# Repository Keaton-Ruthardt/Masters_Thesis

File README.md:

# An Instrumented Baseball for Per-Finger Grip Force Measurement

Reproducibility materials for the MS thesis *An Instrumented Baseball for Per-Finger
Grip Force Measurement: Finger Force Tracks Delivery Effort Rather Than Release Velocity*
(Keaton Ruthardt, MS Computer Science — Data Science, Oral Roberts University, 2026).

A regulation baseball instrumented with four thin-film force sensors under the leather
cover, sampling all channels at 480 Hz and streaming over Bluetooth Low Energy, paired
per pitch with TrackMan radar release velocity.

## What the study found

Measured the way the field currently measures it — with a graded submaximal effort
ladder — grip force predicts release velocity strongly and broadly: index + middle
force at release reaches *r* = 0.59, and 15 of 20 grip features remain significant
after Holm correction.

Holding commanded effort fixed removes that association. Index + middle force at
release falls to *r* = 0.33 (n.s.), and its unique contribution to velocity variance
is **ΔR² = 0.000**, against 0.743 for commanded effort alone. A mixed-effects model
agrees (χ²(1) = 0.47, *p* = 0.49).

Three thumb-dominated features survive Benjamini–Hochberg correction (*q* = 0.035);
none clears family-wise correction, and all are reported as **exploratory**.

The conclusion is that finger grip force, measured under a submaximal effort protocol,
is largely a readout of delivery effort rather than a determinant of release velocity.

## Layout

| Path | Contents |
|---|---|
| `thesis/` | The thesis (`MSCS_Paper.docx`) and its Quarto source, bibliography, and CSL style |
| `defense/` | Defense presentation, including a copy with speaker notes |
| `Masters_Thesis_and_Defense.zip` | Thesis and presentation bundled together |
| `firmware/` | Arduino sketches for the Seeed XIAO nRF52840 |
| `acquisition/` | `ble_logger.py` — BLE client, writes raw counts to CSV |
| `calibration/` | Per-sensor calibration procedure, fitting script, factors, raw captures |
| `analysis/` | Feature extraction, statistics, and figure generation |
| `analysis/results/` | Derived, de-identified data and generated statistical reports |
| `figures/` | Figures as they appear in the thesis |
| `hardware/` | KiCad PCB project, schematic and layout PDFs, bill of materials |
| `docs/` | Illustrated build guides, project plan, proposal |

### Firmware

- `pressure_logger_480/` — **deployed** acquisition firmware. 480 Hz, four samples per packet.
- `pressure_logger/` — earlier 120 Hz single-sample version; the host logger supports both.
- `isolation_test/` — channel-isolation gate.
- `sensor_test/`, `single_sensor/`, `calibrate_sensors/` — bench-check sketches.

Built with the Arduino IDE and the Seeed nRF52 **mbed-enabled** board package. The
non-mbed package fails to link.

## Wire protocol

The pressure characteristic carries a **36-byte packet**: a 32-bit unsigned microsecond
timestamp for the first sample in the batch, followed by four sample groups of four
16-bit unsigned ADC values each, little-endian, in channel order S1 through S4. Sample
*k* within a batch occurs at the batch timestamp plus *k* × 2083 µs.

The earlier firmware sends a 12-byte packet: a 32-bit millisecond timestamp followed by
four 16-bit ADC values. `ble_logger.py` derives the batch size from the packet length
and works against either version without modification.

## Data dictionary

Each logged CSV row contains:

| Column | Meaning |
|---|---|
| `wall_iso` | Host wall-clock time, ISO 8601, UTC |
| `wall_unix_ms` | Host wall-clock time, integer ms since the Unix epoch |
| `ball_t_ms` | The instrument's own timebase in ms — **the authoritative timing column** |
| `s1`–`s4` | Raw ADC counts, 0–4095, in channel order |
| `s1_N`–`s4_N` | Convenience force values in newtons |
| `marker` | Operator-typed per-pitch tag (pitch id, effort, outcome) |

Raw counts are the archived source of truth. Calibration is applied downstream in
analysis, never on the ball, so it can be revised without re-collecting data.

## Force conversion

For a sensor of resistance *R*ₛ in series with a fixed 10 kΩ resistor, the divider node
read by the 12-bit ADC gives a conductance ratio

```
G = ADC / (4095 - ADC)
F = c * G
```

where *c* is the per-sensor calibration factor in `calibration/calfactors_v3.csv`,
fitted through the origin by least squares over twenty applied-mass trials per sensor
(R² = 0.961 to 0.995).

## Reproducing the analysis

```bash
pip install numpy pandas scipy statsmodels matplotlib
cd analysis
python thesis_analysis_v2.py     # feature extraction -> results/
python advanced_stats.py         # corrections, variance decomposition, bootstrap
python make_thesis_figures.py    # figures
```

A fixed random seed (20260805) makes every reported *p*-value reproducible: 20,000
permutations and 10,000 bootstrap resamples throughout.

Note that `thesis_analysis_v2.py` reads raw session captures, which are not distributed
here (see below). The derived feature table it produces, `analysis/results/per_pitch_features.csv`,
**is** included, and `advanced_stats.py` and `make_thesis_figures.py` run from it directly.

## Participant data

Raw per-pitch session captures are **not included**, in accordance with the
participant-privacy commitments described in the thesis. Participants consented to their
data being used in the study; that consent did not extend to public redistribution of
raw records.

Derived, de-identified summary data sufficient to reproduce the reported figures and
models are provided in `analysis/results/`. Pitchers are identified only as P1, P2, P3.

## Licensing

- **Code and firmware** — [MIT License](LICENSE)
- **Documentation, figures, and build records** — [CC BY 4.0](LICENSE-DOCS)

Both are permissive and allow reuse with attribution, which is the intent for a
reproducibility release: you should be able to rebuild the instrument and re-run the
analysis without seeking further permission.

Third-party software is used in accordance with its own licenses, none of which impose
copyleft obligations on this project's code. TrackMan, PitchLogic, Kookaburra,
FlexiForce, Tekscan, Seeed, and Nordic Semiconductor are trademarks of their respective
owners, used nominatively to identify the products actually used or discussed. No
endorsement is implied.

## Safety

The instrument places a lithium-polymer cell and rigid electronics inside a ball thrown
at speed. If you rebuild it, read `docs/BALL_INTEGRATION_GUIDE.md` first. Epoxy is poured
in ~15 g layers with each cured before the next, because the exotherm of a single large
pour is a genuine thermal hazard to an enclosed LiPo cell, and the cell is wrapped before
potting. The ball is retired — not repaired — if the cover is breached, the potted block
loosens, the cell swells or fails to hold charge, or the channel-isolation test fails
after an impact. The cell cannot be removed once potted, so retirement means disposal of
the whole assembly through appropriate lithium-battery disposal.

## Citation

```bibtex
@mastersthesis{ruthardt2026instrumented,
  author = {Ruthardt, Keaton},
  title  = {An Instrumented Baseball for Per-Finger Grip Force Measurement:
            Finger Force Tracks Delivery Effort Rather Than Release Velocity},
  school = {Oral Roberts University},
  year   = {2026},
  type   = {MS thesis}
}
```

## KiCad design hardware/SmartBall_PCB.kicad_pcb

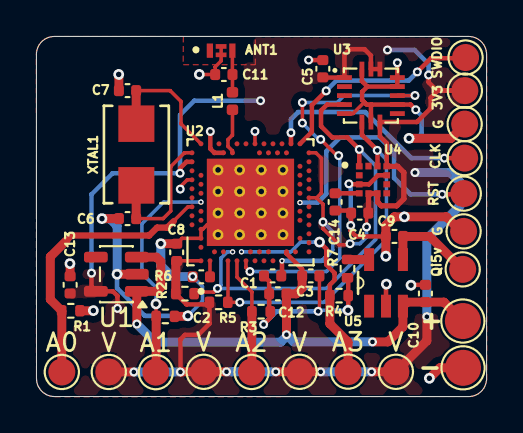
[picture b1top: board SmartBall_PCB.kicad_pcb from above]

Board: 2 copper layers, 25.0 x 20.0 mm, 46 parts (0 on the bottom side), 21 nets.

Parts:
3V3: PAD1; TestPoint_Pad_D1.5mm
+: PAD1; TestPoint_Pad_D2.0mm
-: PAD1; TestPoint_Pad_D2.0mm
A0, A1, A2, A3: PAD1; TestPoint_Pad_D1.5mm
ANT1: ANT016008LCS2442MA1; ANT_ANT016008LCS2442MA1
C1, C2, C4, C5, C14: 100nF/16V; C_0402_1005Metric
C3: 1uF/16V X7R; C_0402_1005Metric
C6, C7: 12pF/16V; C_0402_1005Metric
C8: 10uF/10V X5R; C_0402_1005Metric
C9, C10: 4.7uF/16V X5R; C_0402_1005Metric
C11: 1pF/50V; C_0402_1005Metric
C12, C13: 1uF/10V X7R; C_0402_1005Metric
CLK: PAD1; TestPoint_Pad_D1.5mm
G: PAD1; TestPoint_Pad_D1.5mm
G#2: PAD1; TestPoint_Pad_D1.5mm
L1: 2.2uH; L_0402_1005Metric
Qi5v: PAD1; TestPoint_Pad_D1.5mm
R1, R2, R3, R4: 10K; R_0402_1005Metric
R5, R6: 4.7K; R_0402_1005Metric
R7: 2K; R_0402_1005Metric
RST: PAD1; TestPoint_Pad_D1.5mm
SWDIO: PAD1; TestPoint_Pad_D1.5mm
U1: AP2112K-3.3; SOT-23-5
U2: NRF52840-QIAA-R; XCVR_NRF52840-QIAA-R
U3: H3LIS331DLTR; QFN300X300X100-16N
U4: LIS3MDLTR; XDCR_LIS3MDLTR
U5: MCP73831T-2ACI_OT; SOT95P280X145-5N
V: PAD1; TestPoint_Pad_D1.5mm
V#2, V#3, V#4: PAD1; TestPoint_Pad_D1.5mm
XTAL1: X50328MSB2GI; XTAL_MSB2GI_YXC

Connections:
/AIN0: A0.1 (1_1), R1.1, U2.A12 (P0.02/AIN0)
/AIN1: A1.1 (1_1), R2.1, U2.B13 (P0.03/AIN1)
/AIN2: A2.1 (1_1), R3.1, U2.J1 (P0.04/AIN2)
/AIN3: A3.1 (1_1), R4.1, U2.K2 (P0.05/AIN3)
/BATT_PLUS: +.1 (1_1), C3.1, C10.1, C12.1, U1.1 (VIN), U1.3 (EN), U2.Y2 (VDDH), U5.3 (VBAT)
/I2C_SCL: R6.2, U2.H2 (P0.27), U3.4 (SCL/SPC), U4.1 (SCL/SPC)
/I2C_SDA: R5.2, U2.G1 (P0.26), U3.6 (SDA/SDI/SDO), U4.11 (SDA/SDI/SDO)
/QI_5V: C9.1, Qi5v.1 (1_1), U5.4 (VDD)
/SWD_CLK: CLK.1 (1_1), U2.AA24 (SWDCLK)
/SWD_DIO: SWDIO.1 (1_1), U2.AC24 (SWDIO)
/SWD_RST: RST.1 (1_1), U2.AC13 (P0.18/NRESET)
/WAKE_INT: U2.L1 (P0.06), U3.11 (INT1)
GND: -.1 (1_1), ANT1.2 (gnd), ANT1.3 (gnd), C1.2, C2.2, C3.2, C4.2, C5.2, C6.2, C7.2, C8.2, C9.2, C10.2, C11.2, C12.2, C13.2, C14.2, G.1 (1_1), G#2.1 (1_1), R1.2, R2.2, R3.2, R4.2, R7.2, U1.2 (GND), U2.74 (VSS), U2.74_1, U2.74_2, U2.74_3, U2.74_4, U2.74_5, U2.74_6, U2.74_7, U2.74_8, U2.74_9, U2.74_10, U2.74_11, U2.74_12, U2.74_13, U2.74_14, U2.74_15, U2.74_16, U2.A18 (DEC2), U2.B5 (DEC4), U2.B7 (VSS), U2.D23 (DEC3), U2.F23 (VSS_PA), U2.N24 (DEC5), U3.5 (GND), U3.7 (SDO/SA0), U3.10 (GND), U3.12 (GND), U3.13 (GND), U3.16 (GND), U4.3 (GND), U4.9 (SDO/SA1), U5.2 (VSS)
unnamed: ANT1.4 (FEEDING), C11.1, L1.2
unnamed: L1.1, U2.H23 (ANT)
unnamed: C2.1, U2.C1 (DEC1)
unnamed: C7.1, U2.B24 (XC1), XTAL1.2
unnamed: C6.1, U2.A23 (XC2), XTAL1.1
unnamed: C14.1, U4.4 (C1)
unnamed: R7.1, U5.5 (PROG)
VDD: 3V3.1 (1_1), C1.1, C4.1, C5.1, C8.1, C13.1, R5.1, R6.1, U1.5 (VOUT), U2.A22 (VDD), U2.AD14 (VDD), U2.AD23 (VDD), U2.B1 (VDD), U2.W1 (VDD), U3.1 (VDD_IO), U3.8 (CS), U3.14 (VDD), U3.15 (VDD), U4.5 (VDD), U4.6 (VDD_IO), U4.10 (CS), V.1 (1_1), V#2.1 (1_1), V#3.1 (1_1), V#4.1 (1_1)
